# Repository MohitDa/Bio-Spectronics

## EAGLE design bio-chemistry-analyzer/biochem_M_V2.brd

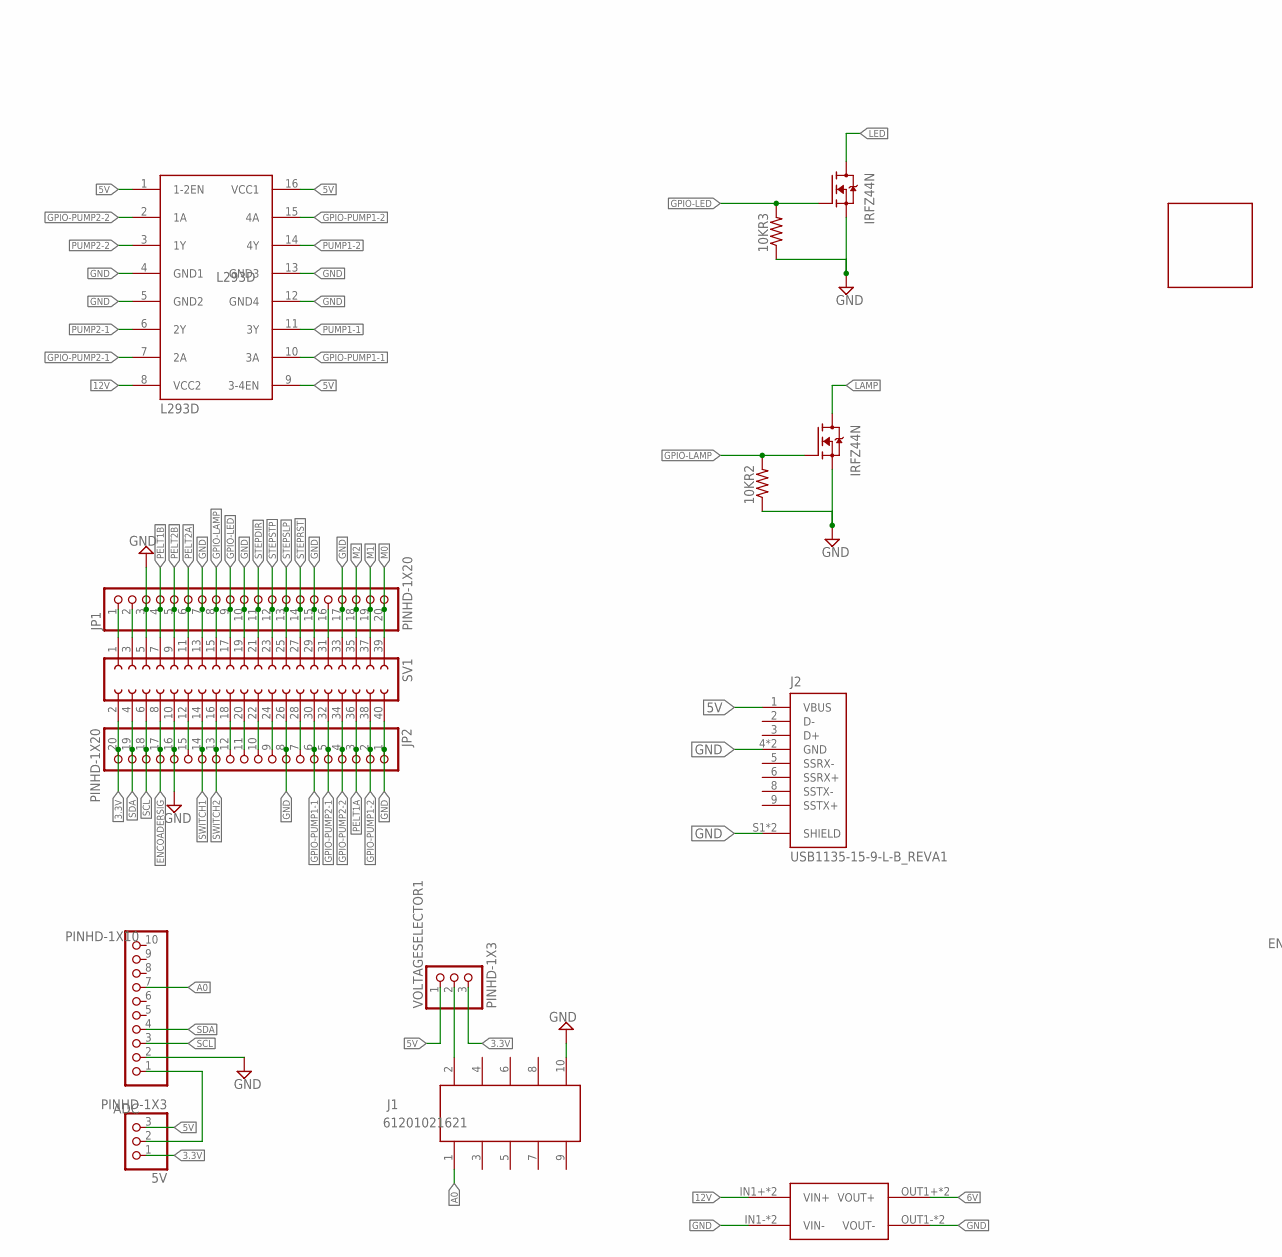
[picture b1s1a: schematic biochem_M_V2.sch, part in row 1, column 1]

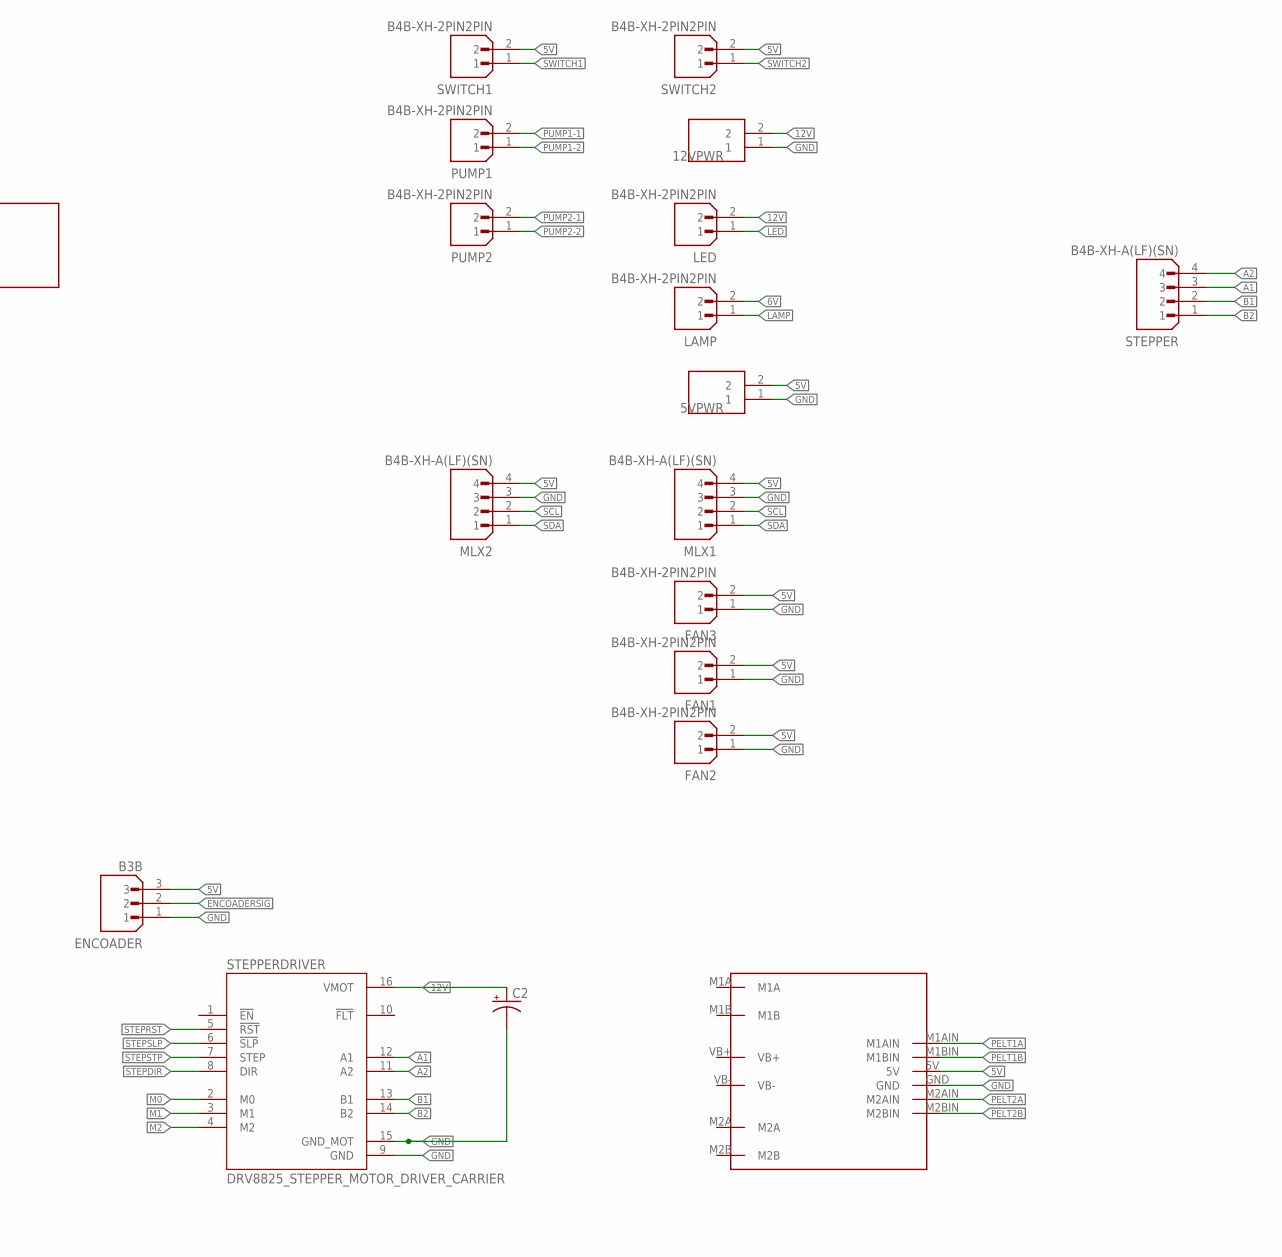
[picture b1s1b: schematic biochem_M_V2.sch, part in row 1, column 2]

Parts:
5V: PINHD-1X3; 1X03
5VPWR, 12VPWR: TB010-508-02BE; CUI_TB010-508-02BE
10KR2, 10KR3: R-US_0204/7; 0204/7
ADC: PINHD-1X10; 1X10
C2: CPOL-USB45181A; B45181A
ENCOADER: B3B
FAN1, FAN2, FAN3: B4B-XH-2PIN2PIN; B4BXH2
J1: 61201021621
J2: USB1135-15-9-L-B_REVA1; GCT_USB1135-15-9-L-B_REVA1
JP1, JP2: PINHD-1X20; 1X20
L293D: L293D; DIL16
LAMP: B4B-XH-2PIN2PIN; B4BXH2
LED: B4B-XH-2PIN2PIN; B4BXH2
MLX1, MLX2: B4B-XH-A(LF)(SN); JST_B4B-XH-A(LF)(SN)
PUMP1, PUMP2: B4B-XH-2PIN2PIN; B4BXH2
Q4-T, Q4-T4: IRFZ44N; TO254P1016X419X2286-3
STEPPER: B4B-XH-A(LF)(SN); JST_B4B-XH-A(LF)(SN)
STEPPERDRIVER: DRV8825_STEPPER_MOTOR_DRIVER_CARRIER; IC_DRV8825_STEPPER_MOTOR_DRIVER_CARRIER
SV1: FE20-2
SWITCH1, SWITCH2: B4B-XH-2PIN2PIN; B4BXH2
U$1: MP1584; DC-BRICK
U$2: MDD3A; FOOTPRINT
U$3: QRBIOS; GITQRBIOSPECTRONICS
VOLTAGESELECTOR1: PINHD-1X3; 1X03

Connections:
3.3V: 5V.1, JP2.20, SV1.2, VOLTAGESELECTOR1.3
5V: 5V.3, 5VPWR.2, ENCOADER.3, FAN1.2, FAN2.2, FAN3.2, J2.1 (VBUS), L293D.1 (1-2EN), L293D.9 (3-4EN), L293D.16 (VCC1), MLX1.4, MLX2.4, SWITCH1.2, SWITCH2.2, U$2.5V, VOLTAGESELECTOR1.1
6V: LAMP.2, U$1.OUT1+ (VOUT+), U$1.OUT2+ (VOUT+)
12V: 12VPWR.2, C2.+, L293D.8 (VCC2), LED.2, STEPPERDRIVER.16 (VMOT), U$1.IN1+ (VIN+), U$1.IN2+ (VIN+)
A0: ADC.7, J1.1
A1: STEPPER.3, STEPPERDRIVER.12 (A1)
A2: STEPPER.4, STEPPERDRIVER.11 (A2)
B1: STEPPER.2, STEPPERDRIVER.13 (B1)
B2: STEPPER.1, STEPPERDRIVER.14 (B2)
ENCOADERSIG: ENCOADER.2, JP2.17, SV1.8
GND: 5VPWR.1, 10KR2.1, 10KR3.1, 12VPWR.1, ADC.2, C2.-, ENCOADER.1, FAN1.1, FAN2.1, FAN3.1, J1.10, J2.4 (GND), J2.7 (GND), J2.S1 (SHIELD), J2.S2 (SHIELD), JP1.3, JP1.7, JP1.10, JP1.15, JP1.17, JP2.1, JP2.8, JP2.16, L293D.4 (GND1), L293D.5 (GND2), L293D.12 (GND4), L293D.13 (GND3), MLX1.3, MLX2.3, Q4-T.3 (S), Q4-T4.3 (S), STEPPERDRIVER.9 (GND), STEPPERDRIVER.15 (GND_MOT), SV1.5, SV1.10, SV1.13, SV1.19, SV1.26, SV1.29, SV1.33, SV1.40, U$1.IN1- (VIN-), U$1.IN2- (VIN-), U$1.OUT1- (VOUT-), U$1.OUT2- (VOUT-), U$2.GND
GPIO-LAMP: 10KR2.2, JP1.8, Q4-T.1 (G), SV1.15
GPIO-LED: 10KR3.2, JP1.9, Q4-T4.1 (G), SV1.17
GPIO-PUMP1-1: JP2.6, L293D.10 (3A), SV1.30
GPIO-PUMP1-2: JP2.2, L293D.15 (4A), SV1.38
GPIO-PUMP2-1: JP2.5, L293D.7 (2A), SV1.32
GPIO-PUMP2-2: JP2.4, L293D.2 (1A), SV1.34
LAMP: LAMP.1, Q4-T.2 (D)
LED: LED.1, Q4-T4.2 (D)
M0: JP1.20, STEPPERDRIVER.2 (M0), SV1.39
M1: JP1.19, STEPPERDRIVER.3 (M1), SV1.37
M2: JP1.18, STEPPERDRIVER.4 (M2), SV1.35
unnamed: JP1.1, SV1.1
unnamed: JP1.2, SV1.3
unnamed: JP2.15, SV1.12
unnamed: J1.2, VOLTAGESELECTOR1.2
unnamed: 5V.2, ADC.1
unnamed: JP1.16, SV1.31
unnamed: JP2.7, SV1.28
unnamed: JP2.9, SV1.24
unnamed: JP2.10, SV1.22
unnamed: JP2.11, SV1.20
unnamed: JP2.12, SV1.18
PELT1A: JP2.3, SV1.36, U$2.M1AIN
PELT1B: JP1.4, SV1.7, U$2.M1BIN
PELT2A: JP1.6, SV1.11, U$2.M2AIN
PELT2B: JP1.5, SV1.9, U$2.M2BIN
PUMP1-1: L293D.11 (3Y), PUMP1.2
PUMP1-2: L293D.14 (4Y), PUMP1.1
PUMP2-1: L293D.6 (2Y), PUMP2.2
PUMP2-2: L293D.3 (1Y), PUMP2.1
SCL: ADC.3, JP2.18, MLX1.2, MLX2.2, SV1.6
SDA: ADC.4, JP2.19, MLX1.1, MLX2.1, SV1.4
STEPDIR: JP1.11, STEPPERDRIVER.8 (DIR), SV1.21
STEPRST: JP1.14, STEPPERDRIVER.5 (!RST), SV1.27
STEPSLP: JP1.13, STEPPERDRIVER.6 (!SLP), SV1.25
STEPSTP: JP1.12, STEPPERDRIVER.7 (STEP), SV1.23
SWITCH1: JP2.14, SV1.14, SWITCH1.1
SWITCH2: JP2.13, SV1.16, SWITCH2.1

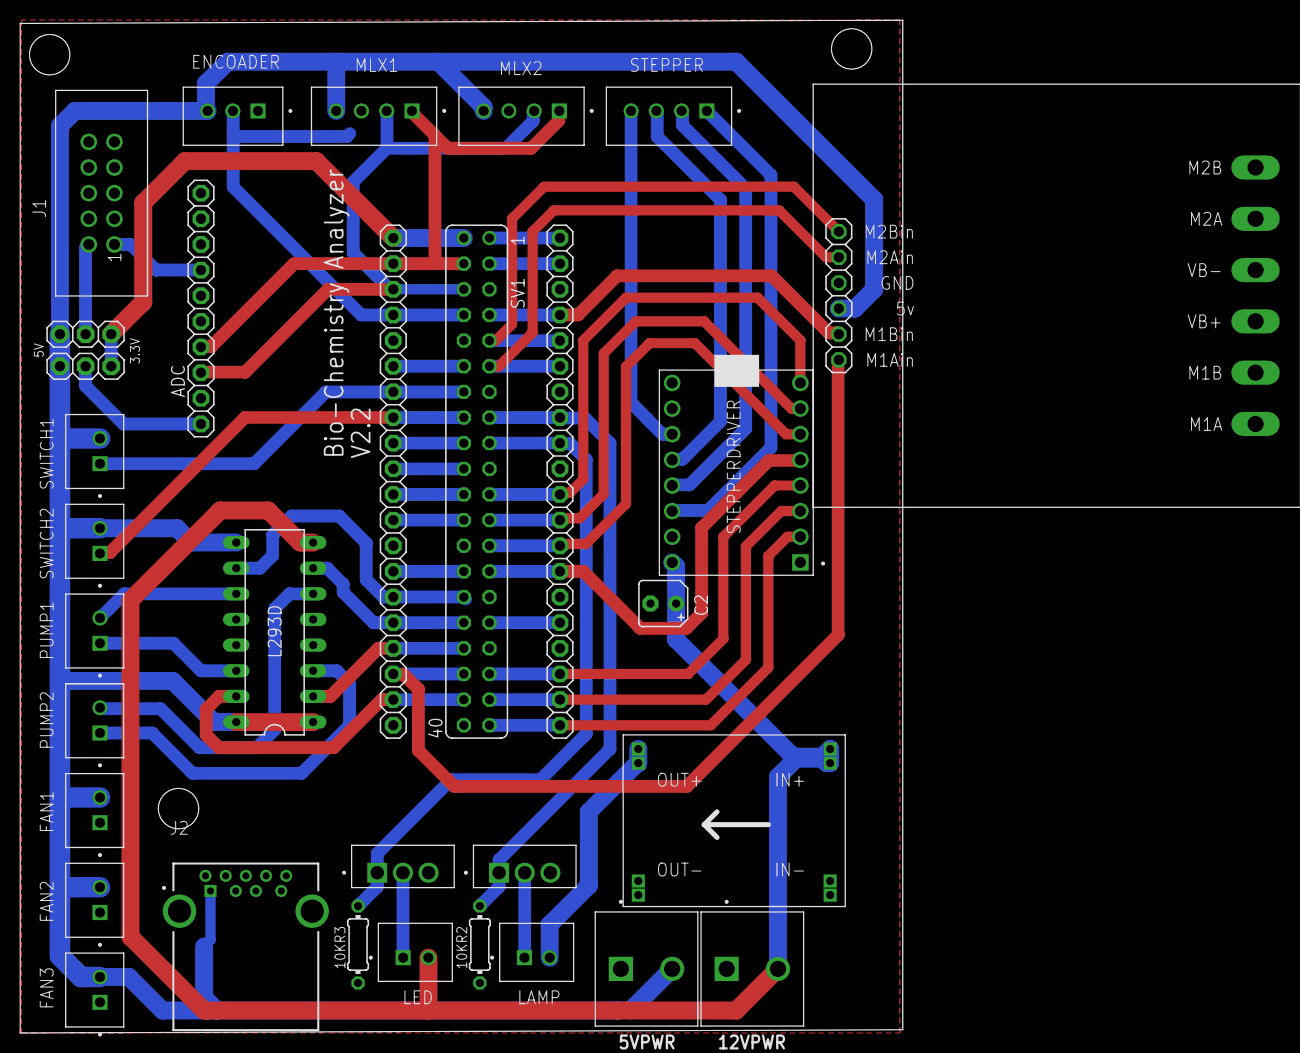
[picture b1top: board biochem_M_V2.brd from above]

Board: 2 copper layers, 87.4 x 100.3 mm, 33 parts (0 on the bottom side), 49 nets.

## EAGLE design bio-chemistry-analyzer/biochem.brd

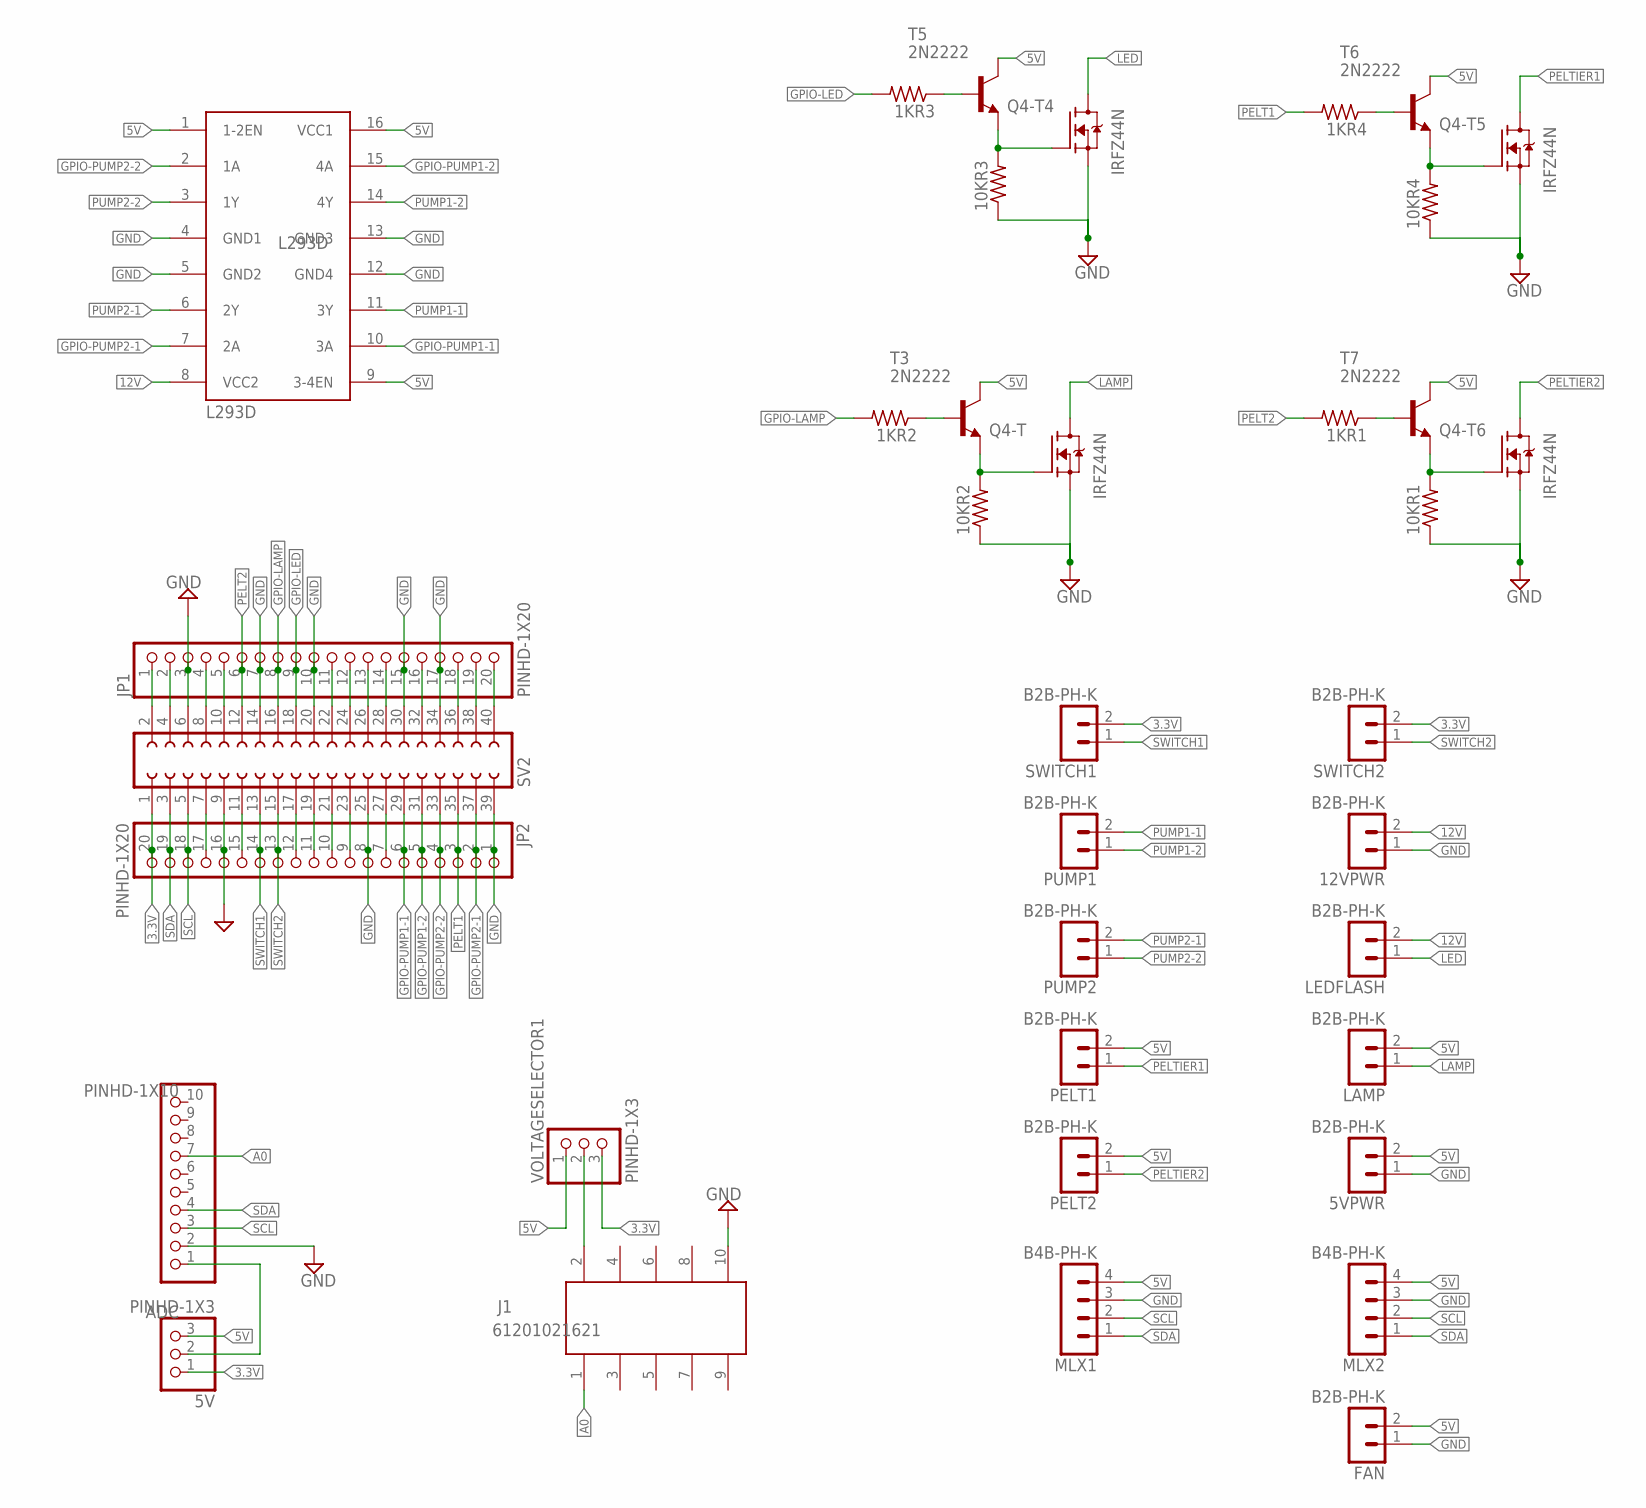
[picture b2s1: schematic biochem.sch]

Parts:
1KR1, 1KR2, 1KR3, 1KR4, 10KR1, 10KR2, 10KR3, 10KR4: R-US_0204/7; 0204/7
5V: PINHD-1X3; 1X03
5VPWR, 12VPWR: B2B-PH-K
ADC: PINHD-1X10; 1X10
FAN: B2B-PH-K
J1: 61201021621
JP1, JP2: PINHD-1X20; 1X20
L293D: L293D; DIL16
LAMP: B2B-PH-K
LEDFLASH: B2B-PH-K
MLX1, MLX2: B4B-PH-K
PELT1, PELT2: B2B-PH-K
PUMP1, PUMP2: B2B-PH-K
Q4-T, Q4-T4, Q4-T5, Q4-T6: IRFZ44N; TO254P1016X419X2286-3
SV2: FE20-2
SWITCH1, SWITCH2: B2B-PH-K
T3, T5, T6, T7: 2N2222; TO92-EBC-OVAL
VOLTAGESELECTOR1: PINHD-1X3; 1X03

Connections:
3.3V: 5V.1, JP2.20, SV2.1, SWITCH1.2, SWITCH2.2, VOLTAGESELECTOR1.3
5V: 5V.3, 5VPWR.2, FAN.2, L293D.1 (1-2EN), L293D.9 (3-4EN), L293D.16 (VCC1), LAMP.2, MLX1.4, MLX2.4, PELT1.2, PELT2.2, T3.C, T5.C, T6.C, T7.C, VOLTAGESELECTOR1.1
12V: 12VPWR.2, L293D.8 (VCC2), LEDFLASH.2
A0: ADC.7, J1.1
ENCODERSIG: JP2.17, SV2.7
GND: 5VPWR.1, 10KR1.1, 10KR2.1, 10KR3.1, 10KR4.1, 12VPWR.1, ADC.2, FAN.1, J1.10, JP1.3, JP1.7, JP1.10, JP1.15, JP1.17, JP2.1, JP2.8, JP2.16, L293D.4 (GND1), L293D.5 (GND2), L293D.12 (GND4), L293D.13 (GND3), MLX1.3, MLX2.3, Q4-T.3 (S), Q4-T4.3 (S), Q4-T5.3 (S), Q4-T6.3 (S), SV2.6, SV2.9, SV2.14, SV2.20, SV2.25, SV2.30, SV2.34, SV2.39
GPIO-LAMP: 1KR2.2, JP1.8, SV2.16
GPIO-LED: 1KR3.2, JP1.9, SV2.18
GPIO-PUMP1-1: JP2.6, L293D.10 (3A), SV2.29
GPIO-PUMP1-2: JP2.5, L293D.15 (4A), SV2.31
GPIO-PUMP2-1: JP2.2, L293D.7 (2A), SV2.37
GPIO-PUMP2-2: JP2.4, L293D.2 (1A), SV2.33
LAMP: LAMP.1, Q4-T.2 (D)
LED: LEDFLASH.1, Q4-T4.2 (D)
M0: JP1.11, SV2.22
M1: JP1.12, SV2.24
M2: JP1.13, SV2.26
unnamed: JP1.1, SV2.2
unnamed: JP1.2, SV2.4
unnamed: JP1.4, SV2.8
unnamed: 10KR2.2, Q4-T.1 (G), T3.E
unnamed: 1KR2.1, T3.B
unnamed: JP1.5, SV2.10
unnamed: J1.2, VOLTAGESELECTOR1.2
unnamed: 5V.2, ADC.1
unnamed: 10KR3.2, Q4-T4.1 (G), T5.E
unnamed: 1KR3.1, T5.B
unnamed: 10KR4.2, Q4-T5.1 (G), T6.E
unnamed: 1KR4.1, T6.B
unnamed: 10KR1.2, Q4-T6.1 (G), T7.E
unnamed: 1KR1.1, T7.B
unnamed: JP1.14, SV2.28
unnamed: JP1.16, SV2.32
unnamed: JP2.7, SV2.27
unnamed: JP2.9, SV2.23
unnamed: JP2.10, SV2.21
unnamed: JP2.11, SV2.19
unnamed: JP2.12, SV2.17
PELT1: 1KR4.2, JP2.3, SV2.35
PELT2: 1KR1.2, JP1.6, SV2.12
PELTIER1: PELT1.1, Q4-T5.2 (D)
PELTIER2: PELT2.1, Q4-T6.2 (D)
PUMP1-1: L293D.11 (3Y), PUMP1.2
PUMP1-2: L293D.14 (4Y), PUMP1.1
PUMP2-1: L293D.6 (2Y), PUMP2.2
PUMP2-2: L293D.3 (1Y), PUMP2.1
SCL: ADC.3, JP2.18, MLX1.2, MLX2.2, SV2.5
SDA: ADC.4, JP2.19, MLX1.1, MLX2.1, SV2.3
STEPDIR: JP1.18, SV2.36
STEPRST: JP2.15, SV2.11
STEPSLP: JP1.20, SV2.40
STEPSTP: JP1.19, SV2.38
SWITCH1: JP2.14, SV2.13, SWITCH1.1
SWITCH2: JP2.13, SV2.15, SWITCH2.1

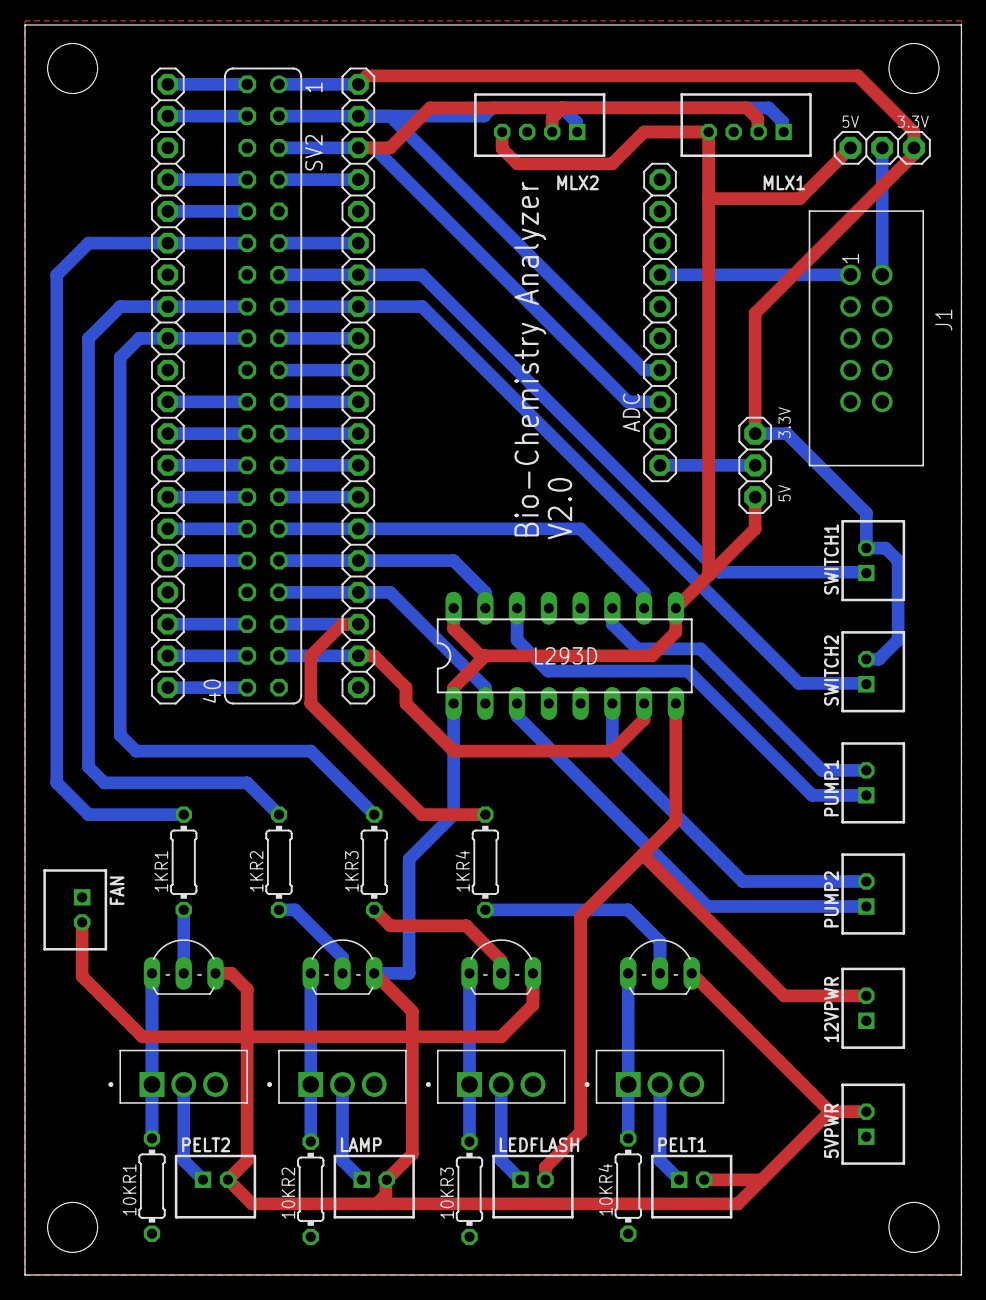
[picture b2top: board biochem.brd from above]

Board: 2 copper layers, 74.9 x 100.0 mm, 37 parts (0 on the bottom side), 54 nets.

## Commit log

2023-04-28 Add files via upload
    28/4/23 commit.
2023-04-28 All Codes Commit 28th April 2023
    Backend algos and frontend is committed at once.
2023-04-28 recommit
2023-05-03 trial commit via VS
2023-05-03 added getting sensitivity, absorance and norm. RGB
2023-05-03 change in db
2023-05-03 changes in db entries
2023-05-03 no change
2023-05-04 4th may
2023-05-06 6th May
2023-05-08 code cleanup with removing ununed comments
2023-05-08 "Test Edited/Added" html Added
2023-05-08 same
2023-05-08 perform test done
2023-05-08 html added
2023-05-08 basic testing feature added
2023-05-09 added flexible input of wavelength for sensitivity value
2023-05-10 10th may
2023-05-11 11th may
2023-05-12 12th may. added popup for buttons
2023-05-15 15th may
2023-05-17 useless copmmit
2023-05-18 18th may
2023-05-20 CHANGES 20th may
2023-05-20 commit2
2023-05-20 changes3
2023-05-22 commit 22nd may
2023-05-23 changes 22nd may
2023-05-23 commit initial 23rd
2023-05-23 Add .gitignore file
2023-05-23 commit 2 (useless)
2023-05-23 useless commit
2023-05-23 add gitignore
2023-05-24 24th may
2023-05-25 25th may
2023-05-30 added eagle files
2023-05-31 PCB Changes
2023-06-01 requirements
2023-06-01 gitignore
2023-06-01 false
